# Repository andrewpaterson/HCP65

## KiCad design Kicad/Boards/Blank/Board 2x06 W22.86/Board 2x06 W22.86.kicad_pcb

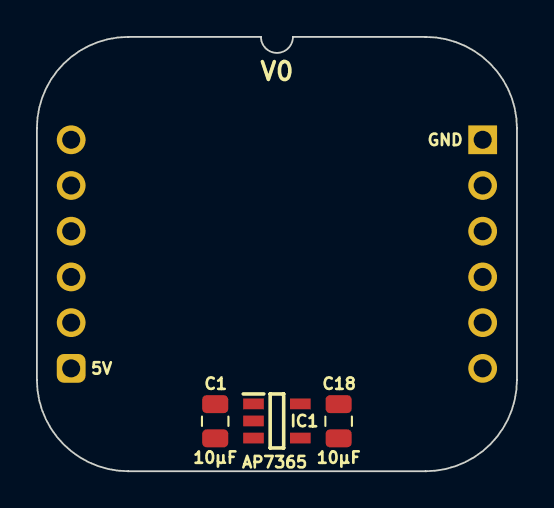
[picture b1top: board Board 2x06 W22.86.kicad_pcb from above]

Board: 2 copper layers, 26.7 x 24.1 mm, 4 parts (0 on the bottom side), 3 nets, no tracks yet.

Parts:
C1, C18: 10µF; C_0805
IC1: AP7365-33WG-7; SOT95P285X130-5N
J7: Board 2x06 W22.86mm; DIP-12_Board_W22.86mm_Alt

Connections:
5V: C1.1, IC1.1 (6VIn), IC1.3 (EN), J7.6
/3.3V: C18.1, IC1.5 (3.3VOut)
GND: C1.2, C18.2, IC1.2 (GND), J7.12

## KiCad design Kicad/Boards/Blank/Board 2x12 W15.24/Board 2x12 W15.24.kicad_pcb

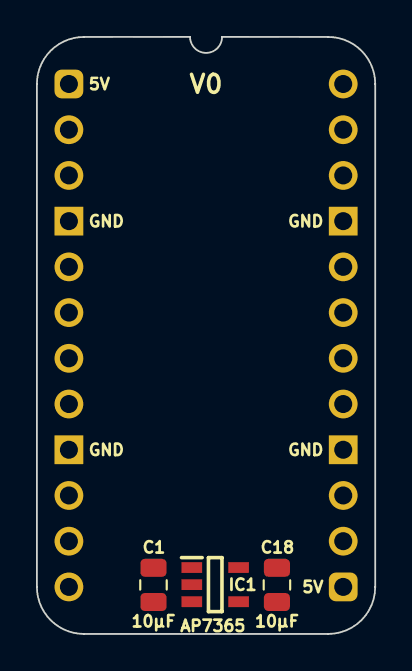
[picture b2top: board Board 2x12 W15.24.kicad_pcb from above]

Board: 2 copper layers, 18.8 x 33.2 mm, 4 parts (0 on the bottom side), 3 nets, no tracks yet.

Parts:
C1, C18: 10µF; C_0805
IC1: AP7365-33WG-7; SOT95P285X130-5N
J1: Board 2x12 W15.24mm; DIP-24_Board_W15.24mm

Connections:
5V: C1.1, IC1.1 (6VIn), IC1.3 (EN), J1.1, J1.13
/3.3V: C18.1, IC1.5 (3.3VOut)
GND: C1.2, C18.2, IC1.2 (GND), J1.4, J1.9, J1.16, J1.21

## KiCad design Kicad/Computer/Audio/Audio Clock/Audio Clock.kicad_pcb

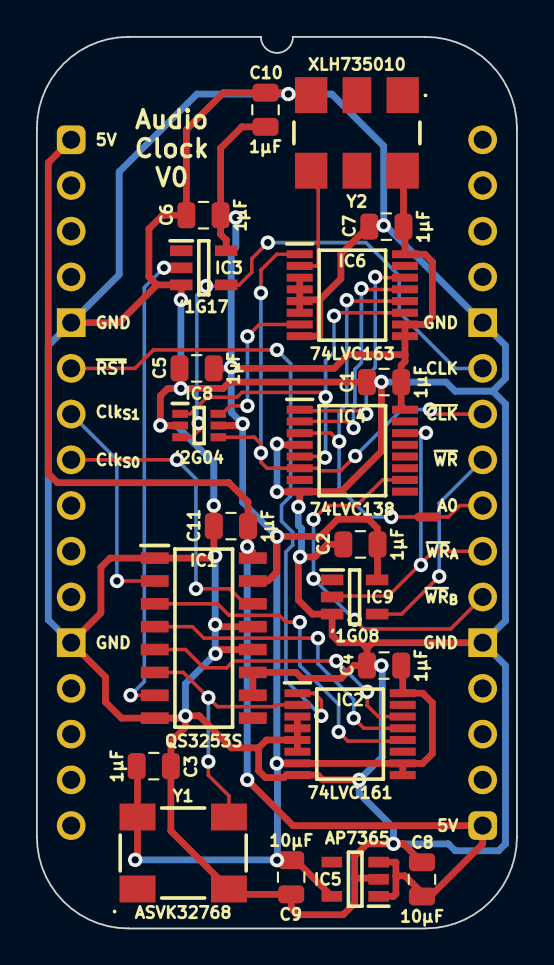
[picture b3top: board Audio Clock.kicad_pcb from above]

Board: 2 copper layers, 26.7 x 49.5 mm, 23 parts (0 on the bottom side), 23 nets.

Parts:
C1, C2, C3, C4, C5, C6, C7, C10, C11: 1μF; C_0805
C8, C9: 10µF; C_0805
IC1: QS3253S1G; SOIC127P602X173-16N
IC2: 74LVC161PW,112; SOP65P640X110-16N
IC3: 74LVC1G17GV,125; SOT95P275X110-5N
IC4: 74LVC138APW-Q100J; SOP65P640X110-16N
IC5: AP7365-33WG-7; SOT95P285X130-5N
IC6: 74LVC163PW,118; SOP65P640X110-16N
IC8: 74LVC2G04GW-Q100H; SOP65P210X110-6N
IC9: 74LVC1G08GV,125; SOT95P275X110-5N
J2: Board 2x16 W22.86mm; DIP-32_Board_W22.86mm
NT1: NetTie; NetTie-2_SMD_Pad0.5mm
Y1: ASVK-32.768KHZ-LJT; ASVK32768KHZLJT
Y2: XLH735010.000000X; XLH735100000000I

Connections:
5V: C8.1, C11.1, IC1.16 (5V), IC5.1 (6VIn), IC5.3 (EN), J2.1, J2.17
/3.3V: C1.1, C2.1, C3.1, C4.1, C5.1, C6.1, C7.1, C9.1, C10.1, IC1.15 (~EB), IC2.7 (CEP), IC2.9 (~PE), IC2.10 (CET), IC2.16 (3V), IC3.5 (3V), IC4.16 (3V), IC5.5 (3.3VOut), IC6.9 (~PE), IC6.10 (CET), IC6.16 (3V), IC8.5 (3V), IC9.5 (3V), Y1.4 (3V), Y2.6 (3V)
/4KHz: IC1.3 (I3A), IC2.12 (Q2)
/8KHz: IC1.4 (I2A), IC2.13 (Q1)
/10MHz: IC6.2 (CP), Y2.4 (OUT)
/16KHz: IC1.5 (I1A), IC2.14 (Q0)
/32KHz: IC1.6 (I0A), IC2.2 (CP), Y1.3 (OUT)
/Q0: IC4.1 (A0), IC6.14 (Q0)
/Q1: IC4.2 (A1), IC6.13 (Q1)
/Q2: IC4.3 (A2), IC6.12 (Q2), NT1.1
/Q3: IC4.5 (~E2), IC6.11 (Q3), IC8.1 (1A)
/~Q3: IC6.7 (CEP), IC8.6 (1Y)
A0: J2.24, NT1.2
CLK: IC3.4 (Y), IC8.3 (2A), J2.27
Clock Select _{S0}: IC1.14 (S0), J2.8
Clock Select _{S1}: IC1.2 (S1), J2.7
GND: C1.2, C2.2, C3.2, C4.2, C5.2, C6.2, C7.2, C8.2, C9.2, C10.2, C11.2, IC1.1 (~EA), IC1.8 (GND), IC1.10 (I0B), IC1.11 (I1B), IC1.12 (I2B), IC1.13 (I3B), IC2.3 (D0), IC2.4 (D1), IC2.5 (D2), IC2.6 (D3), IC2.8 (GND), IC3.3 (GND), IC4.4 (~E1), IC4.8 (GND), IC5.2 (GND), IC6.3 (D0), IC6.4 (D1), IC6.5 (D2), IC6.6 (D3), IC6.8 (GND), IC8.2 (GND), IC9.3 (GND), J2.5, J2.12, J2.21, J2.28, Y1.2 (GND), Y2.3 (GND)
unnamed: IC1.7 (YA), IC3.2 (A)
~CLK: IC4.6 (E3), IC6.1 (~MR), IC8.4 (2Y), J2.26
~Reset: IC2.1 (~MR), J2.6
~WR: IC9.4 (Y), J2.25
~WR_{A}: IC4.14 (~Y1), IC9.2 (A), J2.23
~WR_{B}: IC4.10 (~Y5), IC9.1 (B), J2.22

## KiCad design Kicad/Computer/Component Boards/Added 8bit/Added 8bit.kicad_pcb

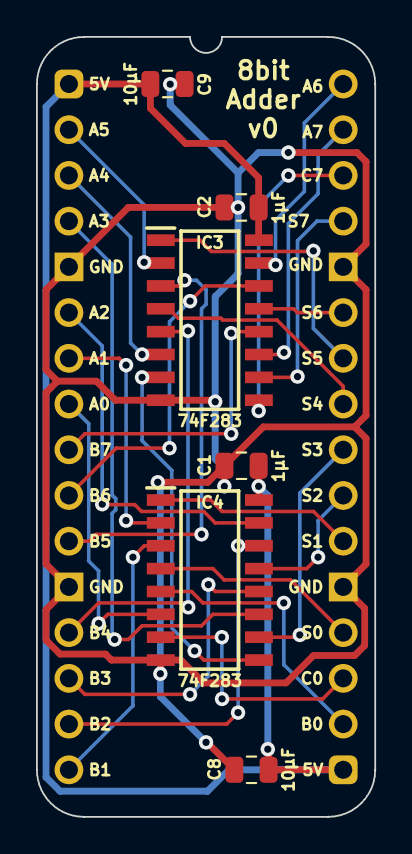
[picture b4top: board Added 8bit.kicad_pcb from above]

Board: 2 copper layers, 18.8 x 43.3 mm, 7 parts (0 on the bottom side), 29 nets.

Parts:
C1, C2: 1μF; C_0805
C8, C9: 10µF; C_0805
IC3, IC4: SN74F283D; SOIC127P600X175-16N
J2: Board 2x16 W15.24mm; DIP-32_Board_W15.24mm

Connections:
5V: C1.1, C2.1, C8.1, C9.1, IC3.16 (5V), IC4.16 (5V), J2.1, J2.17
A_{0}: IC4.6 (B1), J2.8
A_{1}: IC4.2 (B2), J2.7
A_{2}: IC4.15 (B3), J2.6
A_{3}: IC4.11 (B4), J2.4
A_{4}: IC3.6 (B1), J2.3
A_{5}: IC3.2 (B2), J2.2
A_{6}: IC3.15 (B3), J2.32
A_{7}: IC3.11 (B4), J2.31
B_{0}: IC4.5 (A1), J2.18
B_{1}: IC4.3 (A2), J2.16
B_{2}: IC4.14 (A3), J2.15
B_{3}: IC4.12 (A4), J2.14
B_{4}: IC3.5 (A1), J2.13
B_{5}: IC3.3 (A2), J2.11
B_{6}: IC3.14 (A3), J2.10
B_{7}: IC3.12 (A4), J2.9
C_{0}: IC4.7 (C0), J2.19
C_{7}: IC3.9 (C4), J2.30
GND: C1.2, C2.2, C8.2, C9.2, IC3.8 (GND), IC4.8 (GND), J2.5, J2.12, J2.21, J2.28
unnamed: IC3.7 (C0), IC4.9 (C4)
S_{0}: IC4.4 (Σ1), J2.20
S_{1}: IC4.1 (Σ2), J2.22
S_{2}: IC4.13 (Σ3), J2.23
S_{3}: IC4.10 (Σ4), J2.24
S_{4}: IC3.4 (Σ1), J2.25
S_{5}: IC3.1 (Σ2), J2.26
S_{6}: IC3.13 (Σ3), J2.27
S_{7}: IC3.10 (Σ4), J2.29

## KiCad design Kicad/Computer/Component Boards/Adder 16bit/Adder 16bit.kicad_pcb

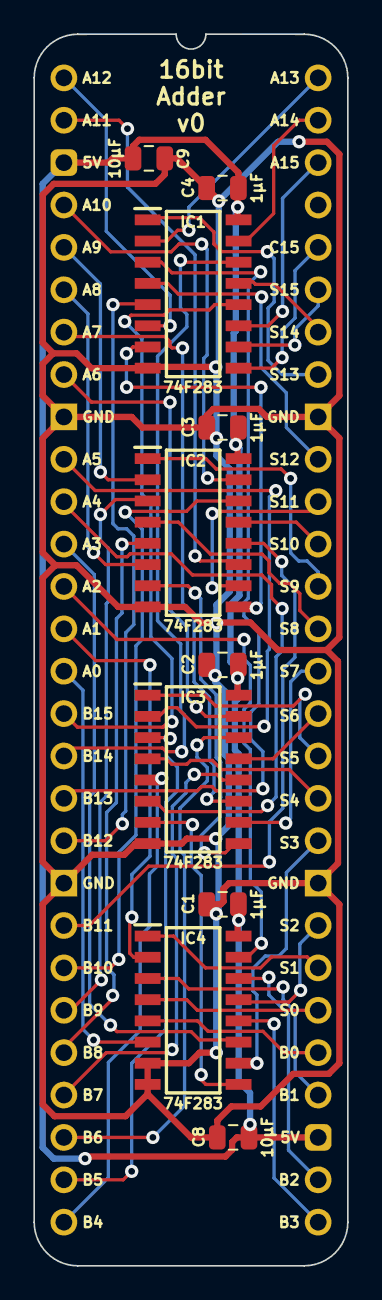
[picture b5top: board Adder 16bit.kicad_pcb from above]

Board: 2 copper layers, 18.8 x 73.8 mm, 11 parts (0 on the bottom side), 54 nets.

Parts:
C1, C2, C3, C4: 1μF; C_0805
C8, C9: 10µF; C_0805
IC1, IC2, IC3, IC4: SN74F283D; SOIC127P600X175-16N
J2: Board 2x28 W15.24mm; DIP-56_Board_W15.24mm

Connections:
5V: C1.1, C2.1, C3.1, C4.1, C8.1, C9.1, IC1.16 (5V), IC2.16 (5V), IC3.16 (5V), IC4.16 (5V), J2.3, J2.31
A_{0}: IC4.6 (B1), J2.15
A_{1}: IC4.2 (B2), J2.14
A_{2}: IC4.15 (B3), J2.13
A_{3}: IC4.11 (B4), J2.12
A_{4}: IC3.6 (B1), J2.11
A_{5}: IC3.2 (B2), J2.10
A_{6}: IC3.15 (B3), J2.8
A_{7}: IC3.11 (B4), J2.7
A_{8}: IC2.6 (B1), J2.6
A_{9}: IC2.2 (B2), J2.5
A_{10}: IC2.15 (B3), J2.4
A_{11}: IC2.11 (B4), J2.2
A_{12}: IC1.6 (B1), J2.1
A_{13}: IC1.2 (B2), J2.56
A_{14}: IC1.15 (B3), J2.55
A_{15}: IC1.11 (B4), J2.54
B_{0}: IC4.5 (A1), J2.33
B_{1}: IC4.3 (A2), J2.32
B_{2}: IC4.14 (A3), J2.30
B_{3}: IC4.12 (A4), J2.29
B_{4}: IC3.5 (A1), J2.28
B_{5}: IC3.3 (A2), J2.27
B_{6}: IC3.14 (A3), J2.26
B_{7}: IC3.12 (A4), J2.25
B_{8}: IC2.5 (A1), J2.24
B_{9}: IC2.3 (A2), J2.23
B_{10}: IC2.14 (A3), J2.22
B_{11}: IC2.12 (A4), J2.21
B_{12}: IC1.5 (A1), J2.19
B_{13}: IC1.3 (A2), J2.18
B_{14}: IC1.14 (A3), J2.17
B_{15}: IC1.12 (A4), J2.16
C_{15}: IC1.9 (C4), J2.52
GND: C1.2, C2.2, C3.2, C4.2, C8.2, C9.2, IC1.8 (GND), IC2.8 (GND), IC3.8 (GND), IC4.7 (C0), IC4.8 (GND), J2.9, J2.20, J2.37, J2.48
unnamed: IC1.7 (C0), IC2.9 (C4)
unnamed: IC2.7 (C0), IC3.9 (C4)
unnamed: IC3.7 (C0), IC4.9 (C4)
S_{0}: IC4.4 (Σ1), J2.34
S_{1}: IC4.1 (Σ2), J2.35
S_{2}: IC4.13 (Σ3), J2.36
S_{3}: IC4.10 (Σ4), J2.38
S_{4}: IC3.4 (Σ1), J2.39
S_{5}: IC3.1 (Σ2), J2.40
S_{6}: IC3.13 (Σ3), J2.41
S_{7}: IC3.10 (Σ4), J2.42
S_{8}: IC2.4 (Σ1), J2.43
S_{9}: IC2.1 (Σ2), J2.44
S_{10}: IC2.13 (Σ3), J2.45
S_{11}: IC2.10 (Σ4), J2.46
S_{12}: IC1.4 (Σ1), J2.47
S_{13}: IC1.1 (Σ2), J2.49
S_{14}: IC1.13 (Σ3), J2.50
S_{15}: IC1.10 (Σ4), J2.51

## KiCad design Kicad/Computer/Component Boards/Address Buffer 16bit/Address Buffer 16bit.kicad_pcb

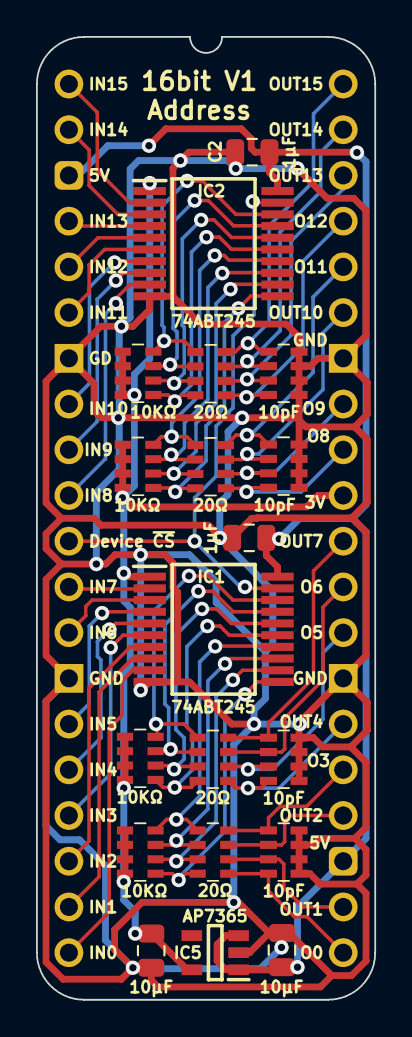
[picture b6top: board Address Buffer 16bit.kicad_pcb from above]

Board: 2 copper layers, 18.8 x 53.5 mm, 20 parts (0 on the bottom side), 52 nets.

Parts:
C1, C2: 1μF; C_0805
C8, C9: 10µF; C_0805
CN1, CN2, CN3, CN4: CA0612KRX7R9BB100
IC1, IC2: SN74ABT245BDBR; SOP65P780X200-20N
IC5: AP7365-33WG-7; SOT95P285X130-5N
J1: Board 2x20 W15.24mm; DIP-40_Board_W15.24mm
RN1, RN2, RN3, RN4: CAY16-103J4LF; CAY16-J4
RN5, RN6, RN9, RN10: CAY16-200J4LF; CAY16-F4

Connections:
3.3V: C9.1, IC1.1 (DIR), IC2.1 (DIR), IC5.5 (3.3VOut), J1.31, RN1.5 (R4), RN1.6 (R3), RN1.7 (R2), RN1.8 (R1), RN2.5 (R4), RN2.6 (R3), RN2.7 (R2), RN2.8 (R1), RN3.5 (R4), RN3.6 (R3), RN3.7 (R2), RN3.8 (R1), RN4.5 (R4), RN4.6 (R3), RN4.7 (R2), RN4.8 (R1)
5V: C1.1, C2.1, C8.1, IC1.20 (5V), IC2.20 (5V), IC5.1 (6VIn), IC5.3 (EN), J1.3, J1.23
/A0: IC1.11 (B7), RN2.1 (R1), RN6.8 (R1)
/A1: IC1.12 (B6), RN2.2 (R2), RN6.7 (R2)
/A2: IC1.13 (B5), RN2.3 (R3), RN6.6 (R3)
/A3: IC1.14 (B4), RN2.4 (R4), RN6.5 (R4)
/A4: IC1.15 (B3), RN1.1 (R1), RN5.8 (R1)
/A5: IC1.16 (B2), RN1.2 (R2), RN5.7 (R2)
/A6: IC1.17 (B1), RN1.3 (R3), RN5.6 (R3)
/A7: IC1.18 (B0), RN1.4 (R4), RN5.5 (R4)
/A8: IC2.11 (B7), RN4.1 (R1), RN9.8 (R1)
/A9: IC2.12 (B6), RN4.2 (R2), RN9.7 (R2)
/A10: IC2.13 (B5), RN4.3 (R3), RN9.6 (R3)
/A11: IC2.14 (B4), RN4.4 (R4), RN9.5 (R4)
/A12: IC2.15 (B3), RN3.1 (R1), RN10.8 (R1)
/A13: IC2.16 (B2), RN3.2 (R2), RN10.7 (R2)
/A14: IC2.17 (B1), RN3.3 (R3), RN10.6 (R3)
/A15: IC2.18 (B0), RN3.4 (R4), RN10.5 (R4)
A0_{IN}: IC1.9 (A7), J1.20
A0_{s}: CN2.4, J1.21, RN6.1 (R1)
A1_{IN}: IC1.8 (A6), J1.19
A1_{s}: CN2.3, J1.22, RN6.2 (R2)
A2_{IN}: IC1.7 (A5), J1.18
A2_{s}: CN2.2, J1.24, RN6.3 (R3)
A3_{IN}: IC1.6 (A4), J1.17
A3_{s}: CN2.1, J1.25, RN6.4 (R4)
A4_{IN}: IC1.5 (A3), J1.16
A4_{s}: CN1.4, J1.26, RN5.1 (R1)
A5_{IN}: IC1.4 (A2), J1.15
A5_{s}: CN1.3, J1.28, RN5.2 (R2)
A6_{IN}: IC1.3 (A1), J1.13
A6_{s}: CN1.2, J1.29, RN5.3 (R3)
A7_{IN}: IC1.2 (A0), J1.12
A7_{s}: CN1.1, J1.30, RN5.4 (R4)
A8_{IN}: IC2.9 (A7), J1.10
A8_{s}: CN3.4, J1.32, RN9.1 (R1)
A9_{IN}: IC2.8 (A6), J1.9
A9_{s}: CN3.3, J1.33, RN9.2 (R2)
A10_{IN}: IC2.7 (A5), J1.8
A10_{s}: CN3.2, J1.35, RN9.3 (R3)
A11_{IN}: IC2.6 (A4), J1.6
A11_{s}: CN3.1, J1.36, RN9.4 (R4)
A12_{IN}: IC2.5 (A3), J1.5
A12_{s}: CN4.4, J1.37, RN10.1 (R1)
A13_{IN}: IC2.4 (A2), J1.4
A13_{s}: CN4.3, J1.38, RN10.2 (R2)
A14_{IN}: IC2.3 (A1), J1.2
A14_{s}: CN4.2, J1.39, RN10.3 (R3)
A15_{IN}: IC2.2 (A0), J1.1
A15_{s}: CN4.1, J1.40, RN10.4 (R4)
Device ~CS: IC1.19 (~OE), IC2.19 (~OE), J1.11
GND: C1.2, C2.2, C8.2, C9.2, CN1.5, CN1.6, CN1.7, CN1.8, CN2.5, CN2.6, CN2.7, CN2.8, CN3.5, CN3.6, CN3.7, CN3.8, CN4.5, CN4.6, CN4.7, CN4.8, IC1.10 (GND), IC2.10 (GND), IC5.2 (GND), J1.7, J1.14, J1.27, J1.34

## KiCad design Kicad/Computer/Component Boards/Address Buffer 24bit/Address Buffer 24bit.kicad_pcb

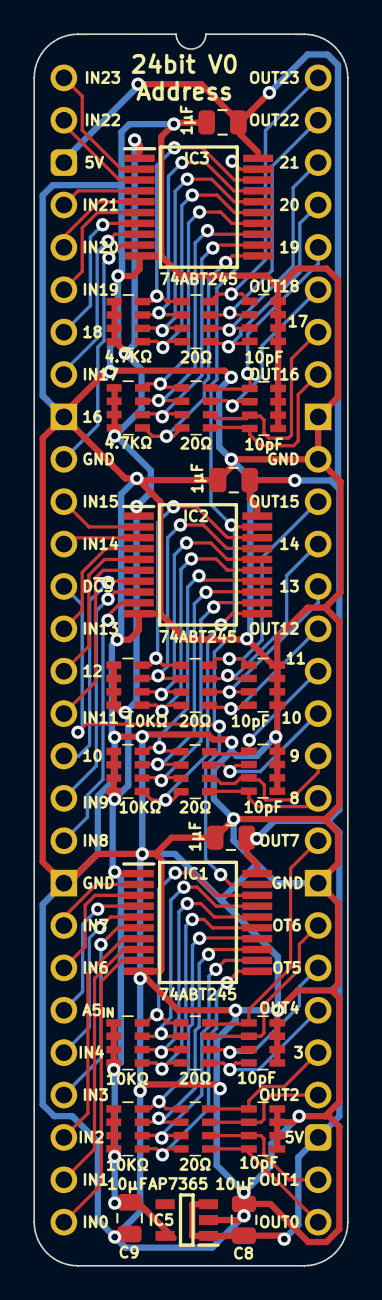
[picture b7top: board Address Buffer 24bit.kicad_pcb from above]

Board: 2 copper layers, 18.8 x 73.8 mm, 28 parts (0 on the bottom side), 76 nets.

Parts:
C1, C2, C3: 1μF; C_0805
C8, C9: 10µF; C_0805
CN1, CN2, CN3, CN4, CN5, CN6: CA0612KRX7R9BB100
IC1, IC2, IC3: SN74ABT245BDBR; SOP65P780X200-20N
IC5: AP7365-33WG-7; SOT95P285X130-5N
J2: Board 2x28 W15.24mm; DIP-56_Board_W15.24mm
RN1, RN2, RN3, RN4: CAY16-103J4LF; CAY16-J4
RN5, RN6, RN9, RN10, RN11, RN12: CAY16-200J4LF; CAY16-F4
RN13, RN14: CAY16-472J4LF; CAY16-F4

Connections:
5V: C1.1, C2.1, C3.1, C8.1, IC1.20 (5V), IC2.20 (5V), IC3.20 (5V), IC5.1 (6VIn), IC5.3 (EN), J2.3, J2.31
/3.3V: C9.1, IC1.1 (DIR), IC2.1 (DIR), IC3.1 (DIR), IC5.5 (3.3VOut), RN1.5 (R4), RN1.6 (R3), RN1.7 (R2), RN1.8 (R1), RN2.5 (R4), RN2.6 (R3), RN2.7 (R2), RN2.8 (R1), RN3.5 (R4), RN3.6 (R3), RN3.7 (R2), RN3.8 (R1), RN4.5 (R4), RN4.6 (R3), RN4.7 (R2), RN4.8 (R1), RN13.5 (R4), RN13.6 (R3), RN13.7 (R2), RN13.8 (R1), RN14.5 (R4), RN14.6 (R3), RN14.7 (R2), RN14.8 (R1)
/A0: IC1.11 (B7), RN2.1 (R1), RN6.8 (R1)
/A1: IC1.12 (B6), RN2.2 (R2), RN6.7 (R2)
/A2: IC1.13 (B5), RN2.3 (R3), RN6.6 (R3)
/A3: IC1.14 (B4), RN2.4 (R4), RN6.5 (R4)
/A4: IC1.15 (B3), RN1.1 (R1), RN5.8 (R1)
/A5: IC1.16 (B2), RN1.2 (R2), RN5.7 (R2)
/A6: IC1.17 (B1), RN1.3 (R3), RN5.6 (R3)
/A7: IC1.18 (B0), RN1.4 (R4), RN5.5 (R4)
/A8: IC2.11 (B7), RN4.1 (R1), RN9.8 (R1)
/A9: IC2.12 (B6), RN4.2 (R2), RN9.7 (R2)
/A10: IC2.13 (B5), RN4.3 (R3), RN9.6 (R3)
/A11: IC2.14 (B4), RN4.4 (R4), RN9.5 (R4)
/A12: IC2.15 (B3), RN3.1 (R1), RN10.8 (R1)
/A13: IC2.16 (B2), RN3.2 (R2), RN10.7 (R2)
/A14: IC2.17 (B1), RN3.3 (R3), RN10.6 (R3)
/A15: IC2.18 (B0), RN3.4 (R4), RN10.5 (R4)
/A16: IC3.11 (B7), RN11.8 (R1), RN14.1 (R1)
/A17: IC3.12 (B6), RN11.7 (R2), RN14.2 (R2)
/A18: IC3.13 (B5), RN11.6 (R3), RN14.3 (R3)
/A19: IC3.14 (B4), RN11.5 (R4), RN14.4 (R4)
/A20: IC3.15 (B3), RN12.8 (R1), RN13.1 (R1)
/A21: IC3.16 (B2), RN12.7 (R2), RN13.2 (R2)
/A22: IC3.17 (B1), RN12.6 (R3), RN13.3 (R3)
/A23: IC3.18 (B0), RN12.5 (R4), RN13.4 (R4)
A0_{IN}: IC1.9 (A7), J2.28
A0_{s}: CN2.4, J2.29, RN6.1 (R1)
A1_{IN}: IC1.8 (A6), J2.27
A1_{s}: CN2.3, J2.30, RN6.2 (R2)
A2_{IN}: IC1.7 (A5), J2.26
A2_{s}: CN2.2, J2.32, RN6.3 (R3)
A3_{IN}: IC1.6 (A4), J2.25
A3_{s}: CN2.1, J2.33, RN6.4 (R4)
A4_{IN}: IC1.5 (A3), J2.24
A4_{s}: CN1.4, J2.34, RN5.1 (R1)
A5_{IN}: IC1.4 (A2), J2.23
A5_{s}: CN1.3, J2.35, RN5.2 (R2)
A6_{IN}: IC1.3 (A1), J2.22
A6_{s}: CN1.2, J2.36, RN5.3 (R3)
A7_{IN}: IC1.2 (A0), J2.21
A7_{s}: CN1.1, J2.38, RN5.4 (R4)
A8_{IN}: IC2.9 (A7), J2.19
A8_{s}: CN3.4, J2.39, RN9.1 (R1)
A9_{IN}: IC2.8 (A6), J2.18
A9_{s}: CN3.3, J2.40, RN9.2 (R2)
A10_{IN}: IC2.7 (A5), J2.17
A10_{s}: CN3.2, J2.41, RN9.3 (R3)
A11_{IN}: IC2.6 (A4), J2.16
A11_{s}: CN3.1, J2.42, RN9.4 (R4)
A12_{IN}: IC2.5 (A3), J2.15
A12_{s}: CN4.4, J2.43, RN10.1 (R1)
A13_{IN}: IC2.4 (A2), J2.14
A13_{s}: CN4.3, J2.44, RN10.2 (R2)
A14_{IN}: IC2.3 (A1), J2.12
A14_{s}: CN4.2, J2.45, RN10.3 (R3)
A15_{IN}: IC2.2 (A0), J2.11
A15_{s}: CN4.1, J2.46, RN10.4 (R4)
A16_{IN}: IC3.9 (A7), J2.10
A16_{s}: CN5.4, J2.49, RN11.1 (R1)
A17_{IN}: IC3.8 (A6), J2.8
A17_{s}: CN5.3, J2.50, RN11.2 (R2)
A18_{IN}: IC3.7 (A5), J2.7
A18_{s}: CN5.2, J2.51, RN11.3 (R3)
A19_{IN}: IC3.6 (A4), J2.6
A19_{s}: CN5.1, J2.52, RN11.4 (R4)
A20_{IN}: IC3.5 (A3), J2.5
A20_{s}: CN6.4, J2.53, RN12.1 (R1)
A21_{IN}: IC3.4 (A2), J2.4
A21_{s}: CN6.3, J2.54, RN12.2 (R2)
A22_{IN}: IC3.3 (A1), J2.2
A22_{s}: CN6.2, J2.55, RN12.3 (R3)
A23_{IN}: IC3.2 (A0), J2.1
A23_{s}: CN6.1, J2.56, RN12.4 (R4)
Device ~CS: IC1.19 (~OE), IC2.19 (~OE), IC3.19 (~OE), J2.13
GND: C1.2, C2.2, C3.2, C8.2, C9.2, CN1.5, CN1.6, CN1.7, CN1.8, CN2.5, CN2.6, CN2.7, CN2.8, CN3.5, CN3.6, CN3.7, CN3.8, CN4.5, CN4.6, CN4.7, CN4.8, CN5.5, CN5.6, CN5.7, CN5.8, CN6.5, CN6.6, CN6.7, CN6.8, IC1.10 (GND), IC2.10 (GND), IC3.10 (GND), IC5.2 (GND), J2.9, J2.20, J2.37, J2.47, J2.48

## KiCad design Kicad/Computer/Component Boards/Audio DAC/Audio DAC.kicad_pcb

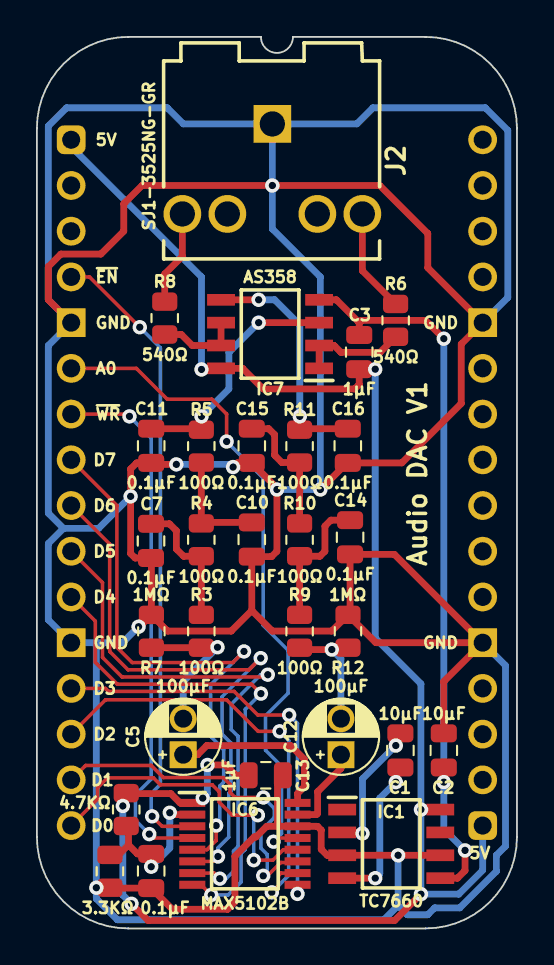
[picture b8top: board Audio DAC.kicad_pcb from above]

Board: 2 copper layers, 26.7 x 49.5 mm, 30 parts (0 on the bottom side), 31 nets.

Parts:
C1, C2: 10µF; C_0805
C3, C13: 1μF; C_0805
C5, C12: 100μF; CP_Radial_D4.0mm_P2.00mm
C6, C7, C10, C11, C14, C15, C16: 0.1μF; C_0805
IC1: TC7660EOA; SOIC127P600X175-8N
IC6: MAX5102BEUE+T; SOP65P640X110-16N
IC7: AS358AMTR-G1; SOIC127P600X175-8N
J1: Board 2x16 W22.86mm; DIP-32_Board_W22.86mm
J2: SJ1-3525NG-GR; SJ13525NGGR
R1: 4.7KΩ; R_0805
R2: 3.3KΩ; R_0805
R3, R4, R5, R9, R10, R11: 100Ω; R_0805
R6, R8: 540Ω; R_0805
R7, R12: 1MΩ; R_0805

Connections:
5V: C3.1, C13.1, IC1.8 (V+), IC6.1 (VDD), IC7.8 (VCC), J1.1, J1.17, R1.1
/-5V: C2.2, C3.2, IC1.5 (VOUT), IC7.4 (GND)
/Line Out Left: J2.3 (L), R6.2
/Line Out Right: J2.2 (R), R8.2
A0: IC6.13 (A0), J1.6
D0: IC6.12 (D0), J1.16
D1: IC6.11 (D1), J1.15
D2: IC6.10 (D2), J1.14
D3: IC6.9 (D3), J1.13
D4: IC6.8 (D4), J1.11
D5: IC6.7 (D5), J1.10
D6: IC6.6 (D6), J1.9
D7: IC6.5 (D7), J1.8
GND: C2.1, C6.1, C7.1, C10.1, C11.1, C13.2, C14.1, C15.1, C16.1, IC1.3 (GND), IC1.6 (LV), IC6.14 (GND), J1.5, J1.12, J1.21, J1.28, J2.1 (GND), R2.1, R7.1, R12.1
unnamed: C5.2, R3.1, R7.2
unnamed: C7.2, R3.2, R4.1
unnamed: C10.2, R4.2, R5.1
unnamed: C12.2, R9.1, R12.2
unnamed: C14.2, R9.2, R10.1
unnamed: C15.2, R10.2, R11.1
unnamed: C1.1, IC1.2 (CAP+)
unnamed: C1.2, IC1.4 (CAP-)
unnamed: C5.1, IC6.16 (OUTA)
unnamed: C12.1, IC6.15 (OUTB)
unnamed: C6.2, IC6.2 (REF), R1.2, R2.2
unnamed: C11.2, IC7.3 (IN_1+), R5.2
unnamed: IC7.1 (OUT_1), IC7.2 (IN_1-), R6.1
unnamed: C16.2, IC7.5 (IN_2+), R11.2
unnamed: IC7.6 (IN_2-), IC7.7 (OUT_2), R8.1
~Enable: IC6.3 (SHDN), J1.4
~WR: IC6.4 (~WR), J1.7
